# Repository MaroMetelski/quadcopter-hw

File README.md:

# Quadcopter flight controller

Brushed DC motor quadcopter flight controller hardware.

Schematics, PCB images and productions files for each release can be found
in https://github.com/MaroMetelski/quadcopter-hw/releases/.

# Revisions

## V1.0

Initial version of the brushed motor flight controller. Main features:

- 30.5x30.5 mm form factor
- Powered with 1S 3.7V battery
- On-board 1S Li-Po charger
- STM32F303RE controller
- Support for 6-channel PWM or 1-channel SBus radio receiver
- BQ274441 fuel gauge
- LSM6DSO 6-axis IMU (accelerometer & gyroscope)

Links:
- [Schematic](https://github.com/MaroMetelski/quadcopter-hw/releases/download/v1.0/quadcopter_v1.0_schematic.pdf)

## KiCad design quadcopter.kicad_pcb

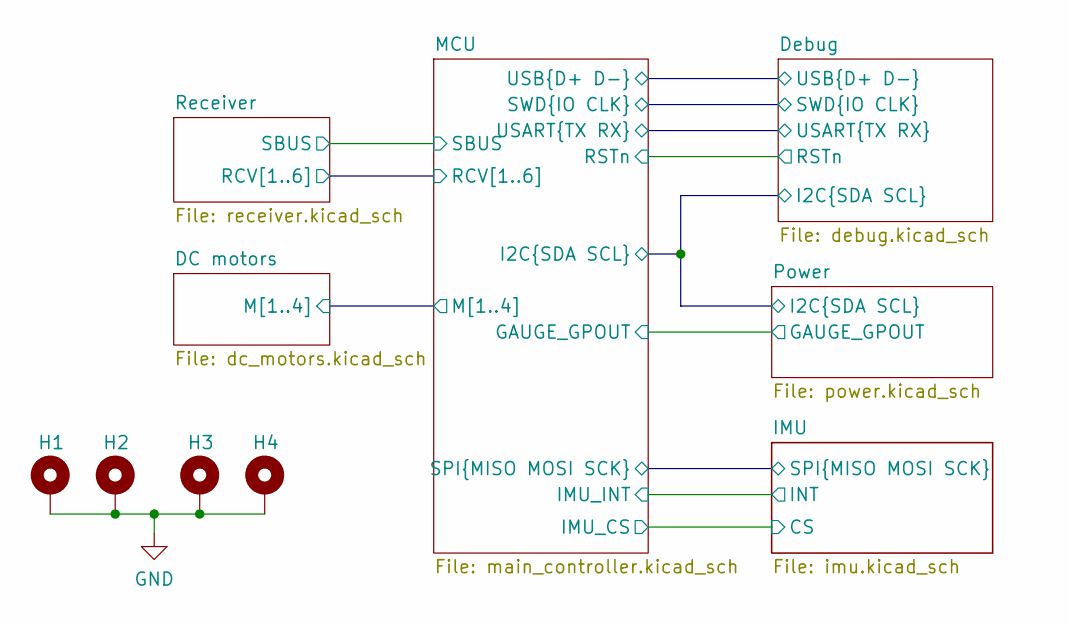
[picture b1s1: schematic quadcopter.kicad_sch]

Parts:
H1, H2, H3, H4: MountingHole_Pad; MountingHole_2.2mm_M2_Pad

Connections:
GND: H1.1, H2.1, H3.1, H4.1; also elsewhere on the board

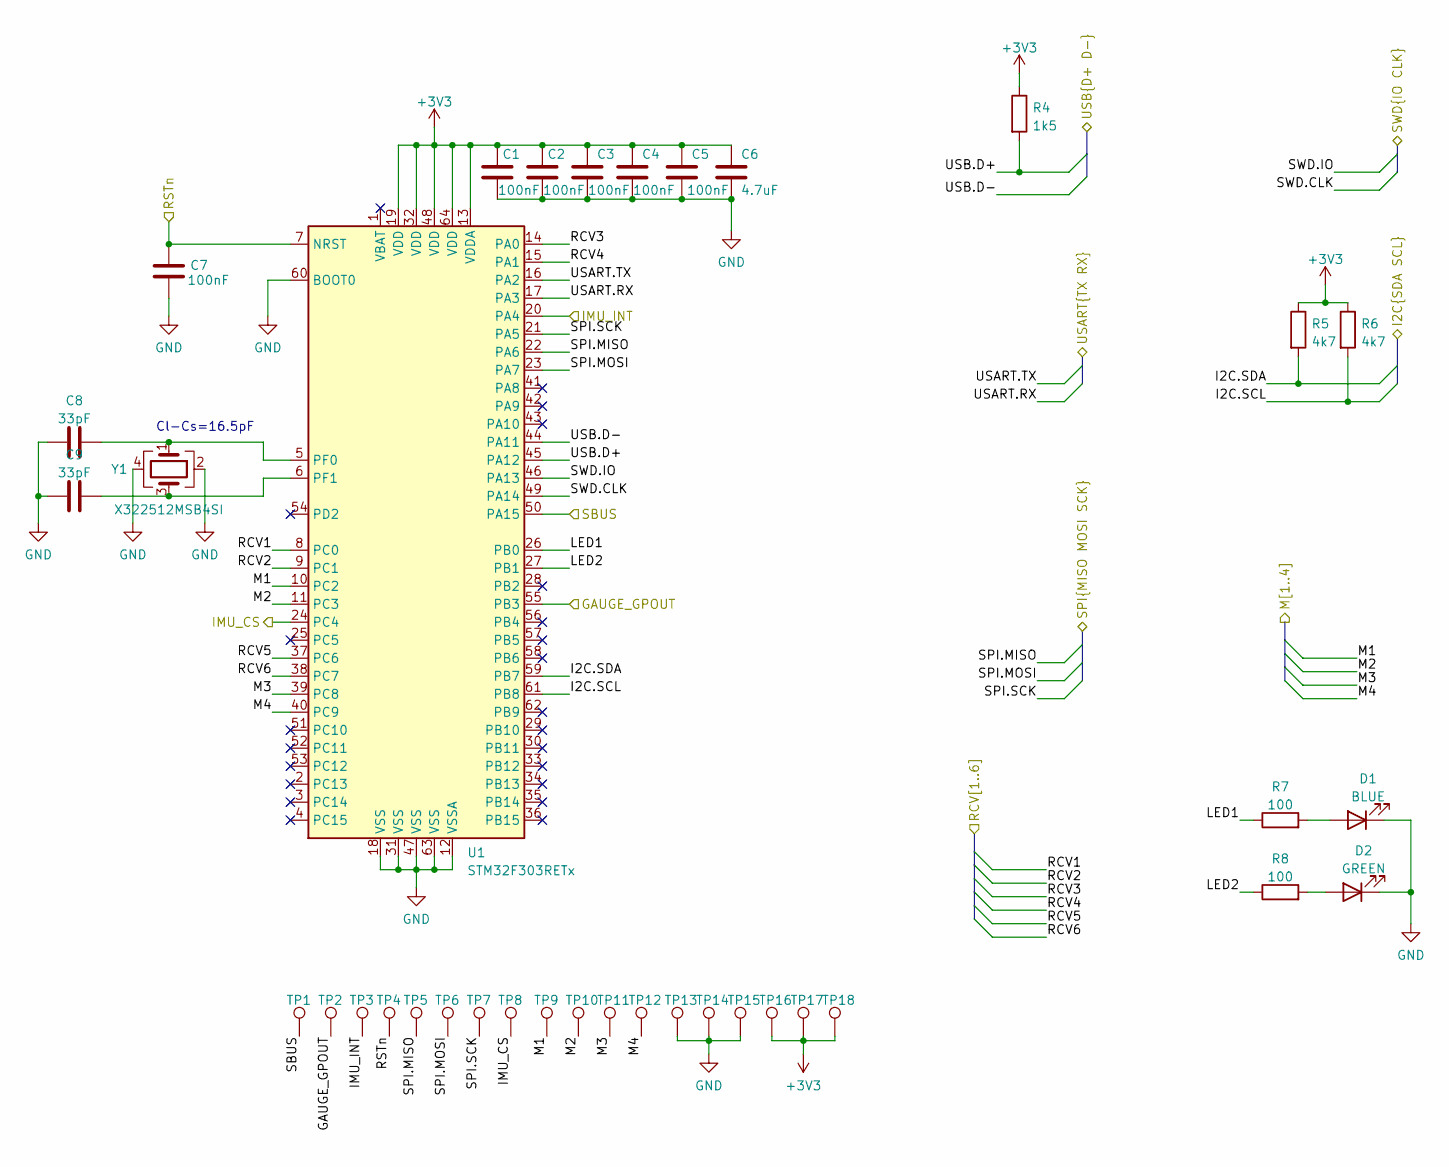
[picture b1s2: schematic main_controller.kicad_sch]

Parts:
C1, C2, C3, C4, C5, C7: 100nF; C_0402_1005Metric; JLC 0402
C6: 4.7uF; C_0402_1005Metric; JLC 0402
C8, C9: 33pF; C_0402_1005Metric; JLC 0402
D1: BLUE; LED_0603_1608Metric; JLC 0603
D2: GREEN; LED_0603_1608Metric; JLC 0603
R4: 1k5; R_0402_1005Metric; JLC 0402
R5, R6: 4k7; R_0402_1005Metric; JLC 0402
R7, R8: 100; R_0402_1005Metric; JLC 0402
TP1, TP2, TP3, TP4, TP5, TP6, TP7, TP8, TP9, TP10, TP11, TP12, TP13, TP14, TP15, TP16, TP17, TP18: TestPoint; TestPoint_Pad_D1.0mm
U1: STM32F303RETx; LQFP-64_10x10mm_P0.5mm; JLC LQFP-64(10x10)
Y1: X322512MSB4SI; Crystal_SMD_3225-4Pin_3.2x2.5mm; JLC SMD3225-4P

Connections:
+3V3: C1.1, C2.1, C3.1, C4.1, C5.1, C6.1, R4.1, R5.1, R6.1, TP16.1, TP17.1, TP18.1, U1.13 (VDDA), U1.19 (VDD), U1.32 (VDD), U1.48 (VDD), U1.64 (VDD); also elsewhere on the board
/DC motors/M1: TP9.1, U1.10 (PC2); also elsewhere on the board
/DC motors/M2: TP10.1, U1.11 (PC3); also elsewhere on the board
/DC motors/M3: TP11.1, U1.39 (PC8); also elsewhere on the board
/DC motors/M4: TP12.1, U1.40 (PC9); also elsewhere on the board
/Debug/I2C.SCL: R6.2, U1.61 (PB8); also elsewhere on the board
/Debug/I2C.SDA: R5.2, U1.59 (PB7); also elsewhere on the board
/Debug/SWD.CLK: U1.49 (PA14); also elsewhere on the board
/Debug/SWD.IO: U1.46 (PA13); also elsewhere on the board
/Debug/USART.RX: U1.17 (PA3); also elsewhere on the board
/Debug/USART.TX: U1.16 (PA2); also elsewhere on the board
/Debug/USB.D+: R4.2, U1.45 (PA12); also elsewhere on the board
/Debug/USB.D-: U1.44 (PA11); also elsewhere on the board
/IMU/SPI.MISO: TP5.1, U1.22 (PA6); also elsewhere on the board
/IMU/SPI.MOSI: TP6.1, U1.23 (PA7); also elsewhere on the board
/IMU/SPI.SCK: TP7.1, U1.21 (PA5); also elsewhere on the board
/MCU/GAUGE_GPOUT: TP2.1, U1.55 (PB3); also elsewhere on the board
/MCU/IMU_CS: TP8.1, U1.24 (PC4); also elsewhere on the board
/MCU/IMU_INT: TP3.1, U1.20 (PA4); also elsewhere on the board
/MCU/LED1: R7.1, U1.26 (PB0)
/MCU/LED2: R8.1, U1.27 (PB1)
/MCU/RCV1: U1.8 (PC0); also elsewhere on the board
/MCU/RCV2: U1.9 (PC1); also elsewhere on the board
/MCU/RCV3: U1.14 (PA0); also elsewhere on the board
/MCU/RCV4: U1.15 (PA1); also elsewhere on the board
/MCU/RCV5: U1.37 (PC6); also elsewhere on the board
/MCU/RCV6: U1.38 (PC7); also elsewhere on the board
/MCU/RSTn: C7.1, TP4.1, U1.7 (NRST); also elsewhere on the board
/MCU/SBUS: TP1.1, U1.50 (PA15); also elsewhere on the board
GND: C1.2, C2.2, C3.2, C4.2, C5.2, C6.2, C7.2, C8.1, C9.1, D1.1 (K), D2.1 (K), TP13.1, TP14.1, TP15.1, U1.12 (VSSA), U1.18 (VSS), U1.31 (VSS), U1.47 (VSS), U1.60 (BOOT0), U1.63 (VSS), Y1.2, Y1.4; also elsewhere on the board
unnamed: C8.2, U1.5 (PF0), Y1.1
unnamed: C9.2, U1.6 (PF1), Y1.3
unnamed: D1.2 (A), R7.2
unnamed: D2.2 (A), R8.2

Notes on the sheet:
Cl-Cs=16.5pF

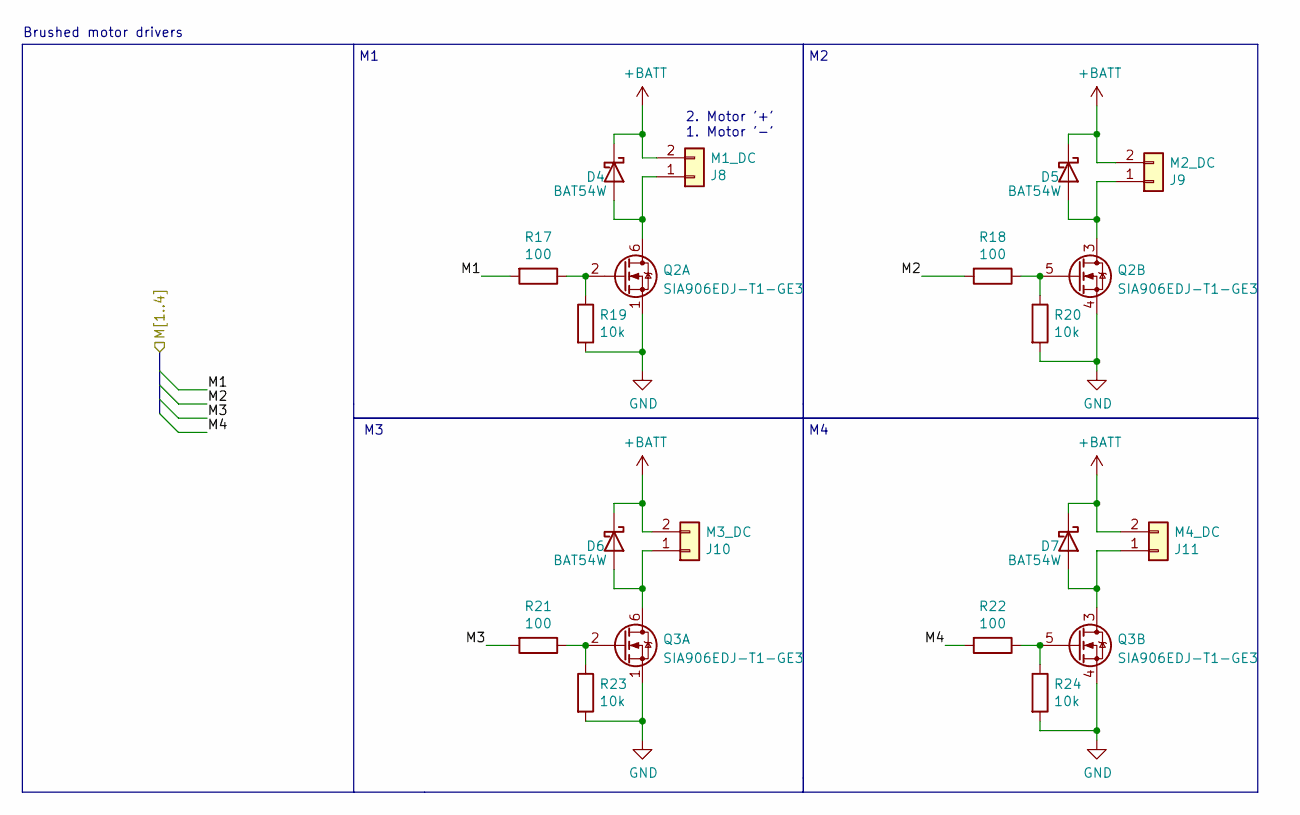
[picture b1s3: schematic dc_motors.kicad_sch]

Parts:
D4, D5, D6, D7: BAT54W; D_SOD-123; LCSC C915628
J8: M1_DC; PinHeader_1x02_P2.54mm_Vertical
J9: M2_DC; PinHeader_1x02_P2.54mm_Vertical
J10: M3_DC; PinHeader_1x02_P2.54mm_Vertical
J11: M4_DC; PinHeader_1x02_P2.54mm_Vertical
Q2, Q3: SIA906EDJ-T1-GE3; Vishay_PowerPAK_SC70-6L_Dual; JLC WSON-6-EP(2x2)
R17, R18, R21, R22: 100; R_0402_1005Metric; JLC 0402
R19, R20, R23, R24: 10k; R_0402_1005Metric; JLC 0402

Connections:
+BATT: D4.1 (K), D5.1 (K), D6.1 (K), D7.1 (K), J8.2, J9.2, J10.2, J11.2; also elsewhere on the board
/DC motors/M1: R17.2; also elsewhere on the board
/DC motors/M2: R18.2; also elsewhere on the board
/DC motors/M3: R21.2; also elsewhere on the board
/DC motors/M4: R22.2; also elsewhere on the board
GND: Q2.1 (S), Q2.4 (S), Q3.1 (S), Q3.4 (S), R19.2, R20.2, R23.2, R24.2; also elsewhere on the board
unnamed: D4.2 (A), J8.1, Q2.6 (D)
unnamed: D5.2 (A), J9.1, Q2.3 (D)
unnamed: D6.2 (A), J10.1, Q3.6 (D)
unnamed: D7.2 (A), J11.1, Q3.3 (D)
unnamed: Q2.2 (G), R17.1, R19.1
unnamed: Q2.5 (G), R18.1, R20.1
unnamed: Q3.2 (G), R21.1, R23.1
unnamed: Q3.5 (G), R22.1, R24.1

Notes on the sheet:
2. Motor '+' 1. Motor '-'
Brushed motor drivers

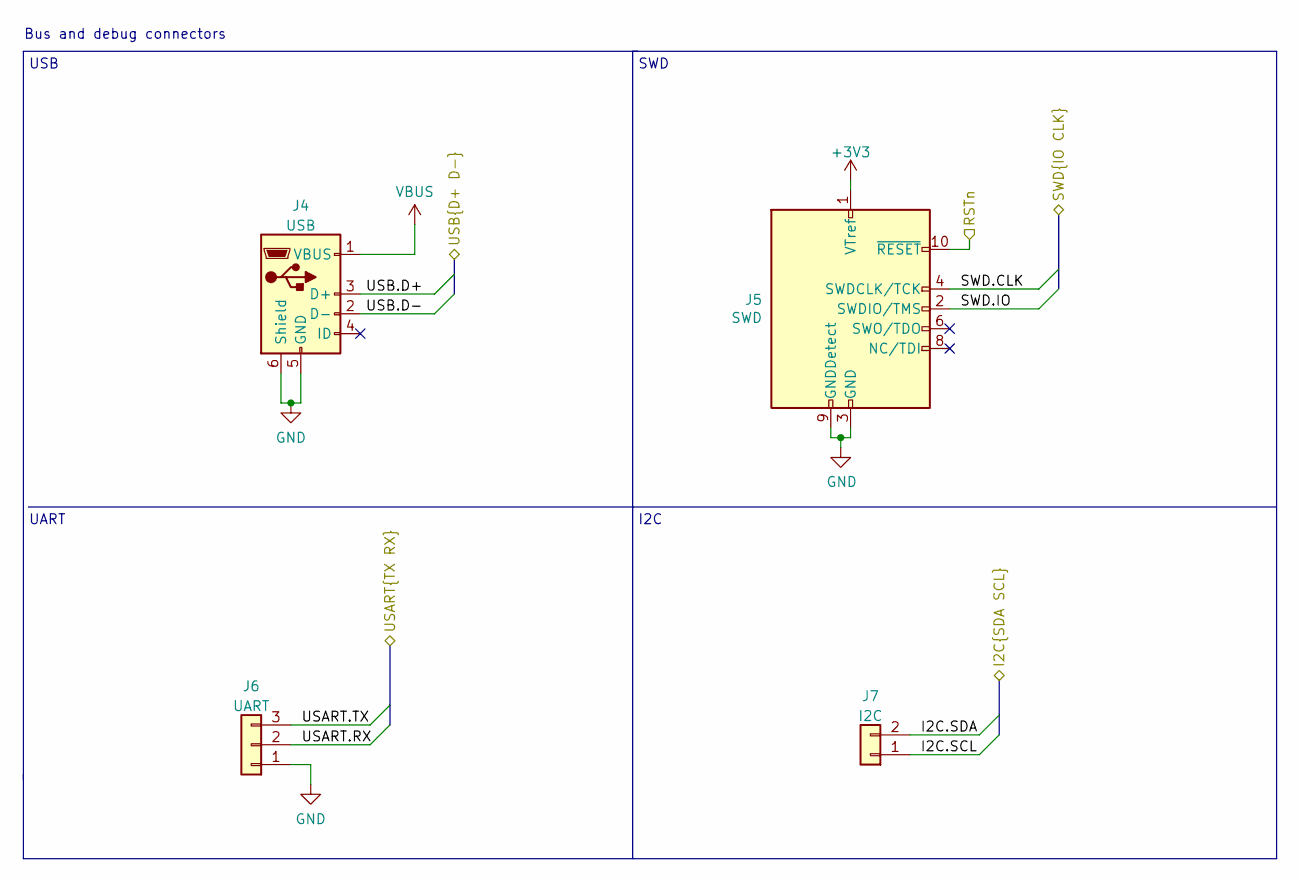
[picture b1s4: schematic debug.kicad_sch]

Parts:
J4: USB; USB_Micro-B_Molex-105017-0001; JLC SMD
J5: SWD; PinHeader_2x05_P1.27mm_Vertical_SMD
J6: UART; PinHeader_1x03_P2.54mm_Vertical
J7: I2C; PinHeader_1x02_P2.54mm_Vertical

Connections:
+3V3: J5.1 (VTref); also elsewhere on the board
/Debug/I2C.SCL: J7.1; also elsewhere on the board
/Debug/I2C.SDA: J7.2; also elsewhere on the board
/Debug/SWD.CLK: J5.4 (SWDCLK/TCK); also elsewhere on the board
/Debug/SWD.IO: J5.2 (SWDIO/TMS); also elsewhere on the board
/Debug/USART.RX: J6.2; also elsewhere on the board
/Debug/USART.TX: J6.3; also elsewhere on the board
/Debug/USB.D+: J4.3 (D+); also elsewhere on the board
/Debug/USB.D-: J4.2 (D-); also elsewhere on the board
/MCU/RSTn: J5.10 (~RESET); also elsewhere on the board
GND: J4.5 (GND), J4.6 (Shield), J5.3 (GND), J5.5 (GND), J5.9 (GNDDetect), J6.1; also elsewhere on the board
VBUS: J4.1 (VBUS); also elsewhere on the board

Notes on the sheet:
Bus and debug connectors
UART
I2C
USB
SWD

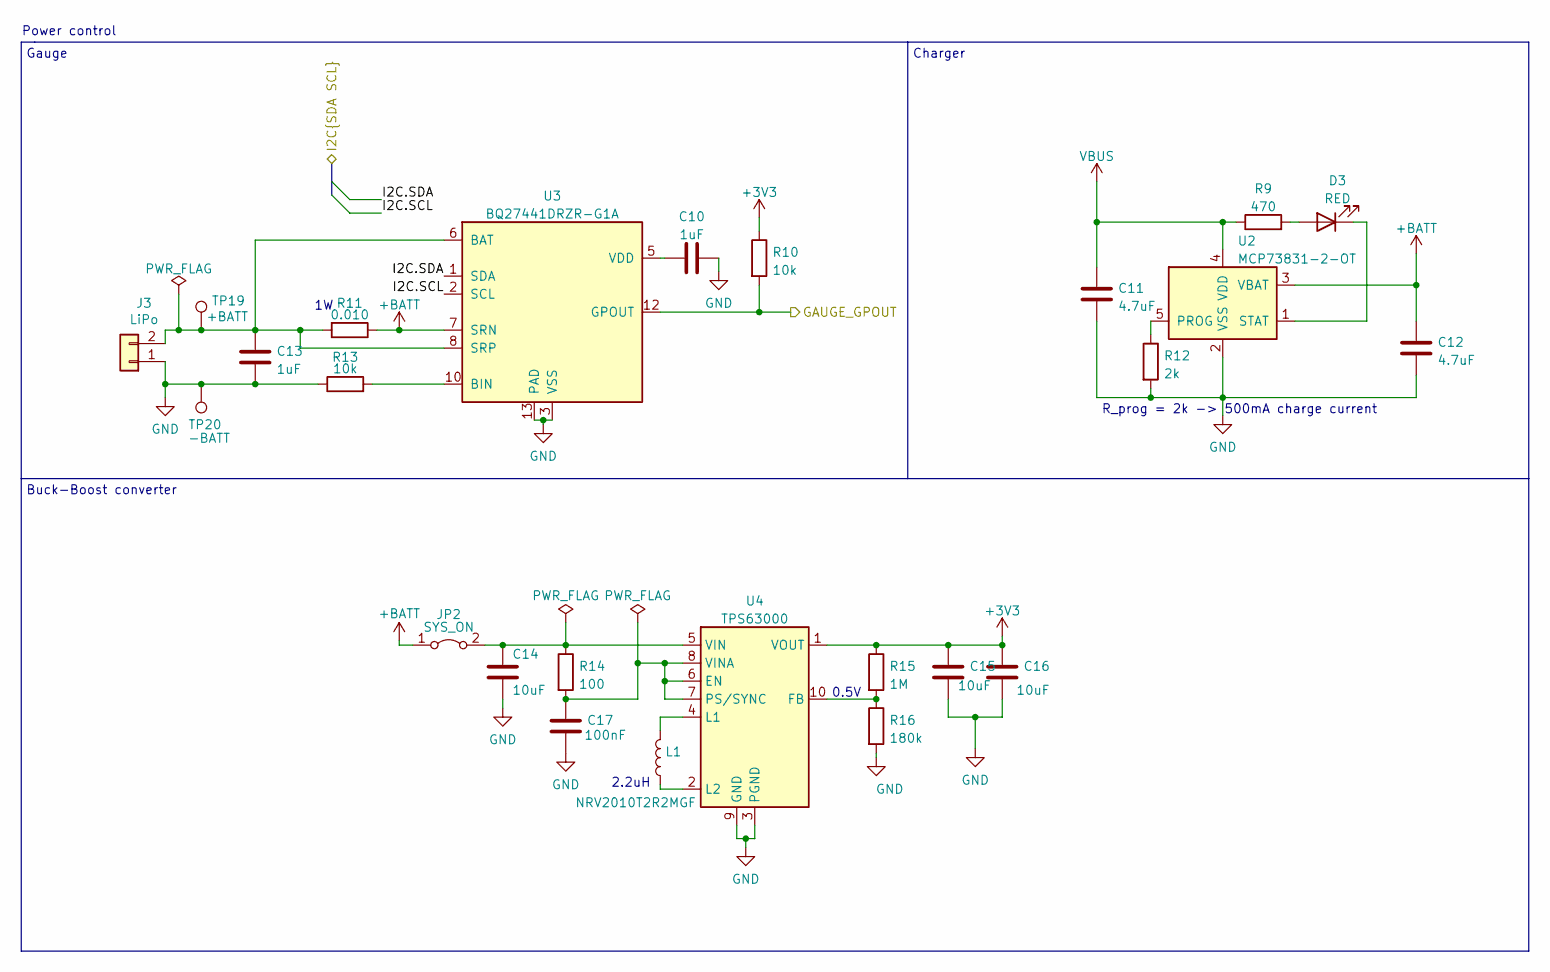
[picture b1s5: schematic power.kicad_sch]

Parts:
C10, C13: 1uF; C_0402_1005Metric; JLC 0402
C11, C12: 4.7uF; C_0402_1005Metric; JLC 0402
C14, C15, C16: 10uF; C_0402_1005Metric; JLC 0402
C17: 100nF; C_0402_1005Metric; JLC 0402
D3: RED; LED_0603_1608Metric; JLC 0603
J3: LiPo; PinHeader_1x02_P2.54mm_Vertical
JP2: SYS_ON; PinHeader_1x02_P2.54mm_Vertical
L1: NRV2010T2R2MGF; L_Taiyo-Yuden_NR-20xx; JLC SMD
R9: 470; R_0402_1005Metric; JLC 0402
R10, R13: 10k; R_0402_1005Metric; JLC 0402
R11: 0.010; R_2010_5025Metric; JLC 2010
R12: 2k; R_0402_1005Metric; JLC 0402
R14: 100; R_0402_1005Metric; JLC 0402
R15: 1M; R_0402_1005Metric; JLC 0402
R16: 180k; R_0402_1005Metric; JLC 0402
TP19: +BATT; TestPoint_Pad_2.0x2.0mm
TP20: -BATT; TestPoint_Pad_2.0x2.0mm
U2: MCP73831-2-OT; SOT-23-5; JLC SOT-23-5
U3: BQ27441DRZR-G1A; Texas_S-PDSO-N12; JLC SON-12-EP(2.5x4)
U4: TPS63000; Texas_DRC0010J_ThermalVias; JLC SON-10-EP(3.1x3.1)

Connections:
+3V3: C15.1, C16.1, R10.1, R15.1, U4.1 (VOUT); also elsewhere on the board
+BATT: C12.1, JP2.1 (A), R11.1, U2.3 (VBAT), U3.7 (SRN); also elsewhere on the board
/Debug/I2C.SCL: U3.2 (SCL); also elsewhere on the board
/Debug/I2C.SDA: U3.1 (SDA); also elsewhere on the board
/MCU/GAUGE_GPOUT: R10.2, U3.12 (GPOUT); also elsewhere on the board
GND: C10.2, C11.2, C12.2, C13.2, C14.2, C15.2, C16.2, C17.2, J3.1, R12.2, R13.1, R16.2, TP20.1, U2.2 (VSS), U3.3 (VSS), U3.13 (PAD), U4.3 (PGND), U4.9 (GND), U4.11 (PGND); also elsewhere on the board
unnamed: C10.1, U3.5 (VDD)
unnamed: C13.1, J3.2, R11.2, TP19.1, U3.6 (BAT), U3.8 (SRP)
unnamed: C14.1, JP2.2 (B), R14.1, U4.5 (VIN)
unnamed: C17.1, R14.2, U4.6 (EN), U4.7 (PS/SYNC), U4.8 (VINA)
unnamed: D3.1 (K), U2.1 (STAT)
unnamed: D3.2 (A), R9.2
unnamed: L1.1, U4.2 (L2)
unnamed: L1.2, U4.4 (L1)
unnamed: R12.1, U2.5 (PROG)
unnamed: R13.2, U3.10 (BIN)
unnamed: R15.2, R16.1, U4.10 (FB)
VBUS: C11.1, R9.1, U2.4 (VDD); also elsewhere on the board

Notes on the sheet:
2.2uH
Charger
R_prog = 2k -> 500mA charge current
Gauge
Power control
Buck-Boost converter
0.5V

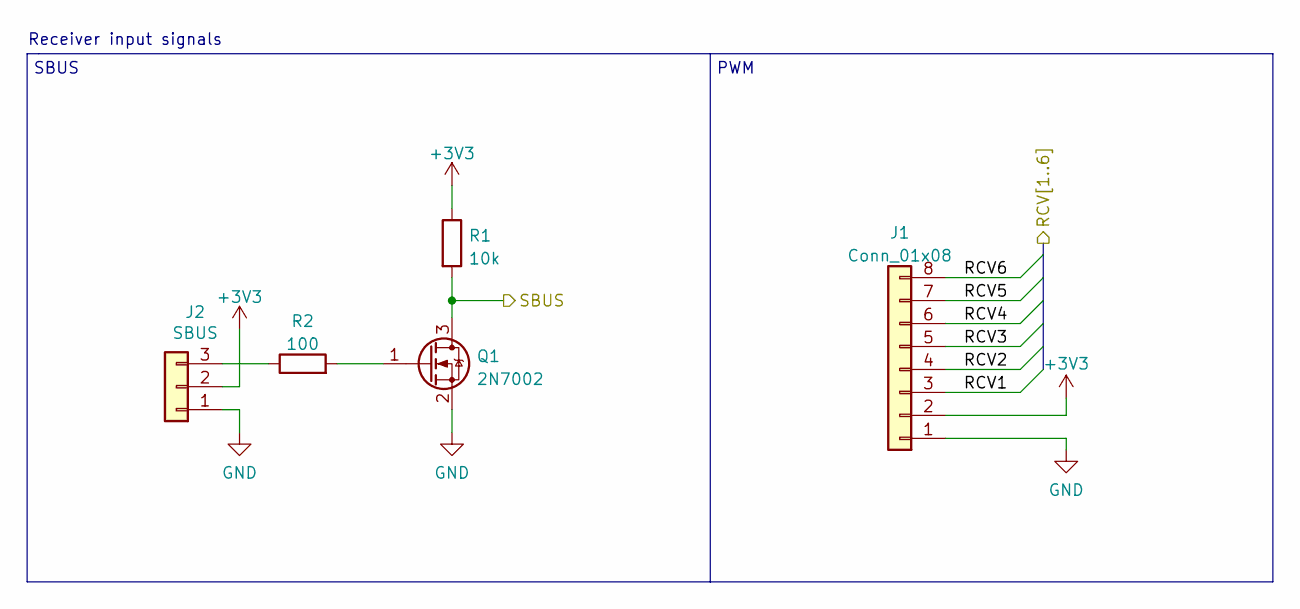
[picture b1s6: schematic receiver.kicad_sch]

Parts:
J1: Conn_01x08; PinHeader_1x08_P2.54mm_Vertical
J2: SBUS; PinHeader_1x03_P2.54mm_Vertical
Q1: 2N7002; SOT-23; JLC SOT-23
R1: 10k; R_0402_1005Metric; JLC 0402
R2: 100; R_0402_1005Metric; JLC 0402

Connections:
+3V3: J1.2, J2.2, R1.1; also elsewhere on the board
/MCU/RCV1: J1.3; also elsewhere on the board
/MCU/RCV2: J1.4; also elsewhere on the board
/MCU/RCV3: J1.5; also elsewhere on the board
/MCU/RCV4: J1.6; also elsewhere on the board
/MCU/RCV5: J1.7; also elsewhere on the board
/MCU/RCV6: J1.8; also elsewhere on the board
/MCU/SBUS: Q1.3 (D), R1.2; also elsewhere on the board
GND: J1.1, J2.1, Q1.2 (S); also elsewhere on the board
unnamed: J2.3, R2.1
unnamed: Q1.1 (G), R2.2

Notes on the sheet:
Receiver input signals
PWM
SBUS

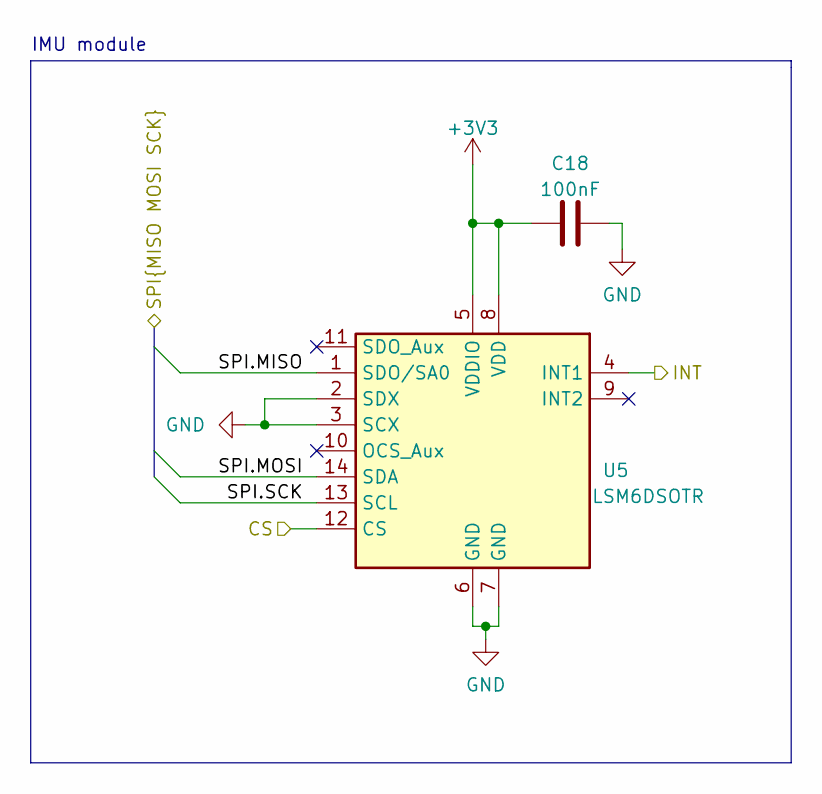
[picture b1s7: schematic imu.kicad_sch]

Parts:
C18: 100nF; C_0402_1005Metric; JLC 0402
U5: LSM6DSOTR; LGA-14_3x2.5mm_P0.5mm_LayoutBorder3x4y; JLC LGA-14(2.5x3)

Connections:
+3V3: C18.2, U5.5 (VDDIO), U5.8 (VDD); also elsewhere on the board
/IMU/SPI.MISO: U5.1 (SDO/SA0); also elsewhere on the board
/IMU/SPI.MOSI: U5.14 (SDA); also elsewhere on the board
/IMU/SPI.SCK: U5.13 (SCL); also elsewhere on the board
/MCU/IMU_CS: U5.12 (CS); also elsewhere on the board
/MCU/IMU_INT: U5.4 (INT1); also elsewhere on the board
GND: C18.1, U5.2 (SDX), U5.3 (SCX), U5.6 (GND), U5.7 (GND); also elsewhere on the board

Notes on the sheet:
IMU module

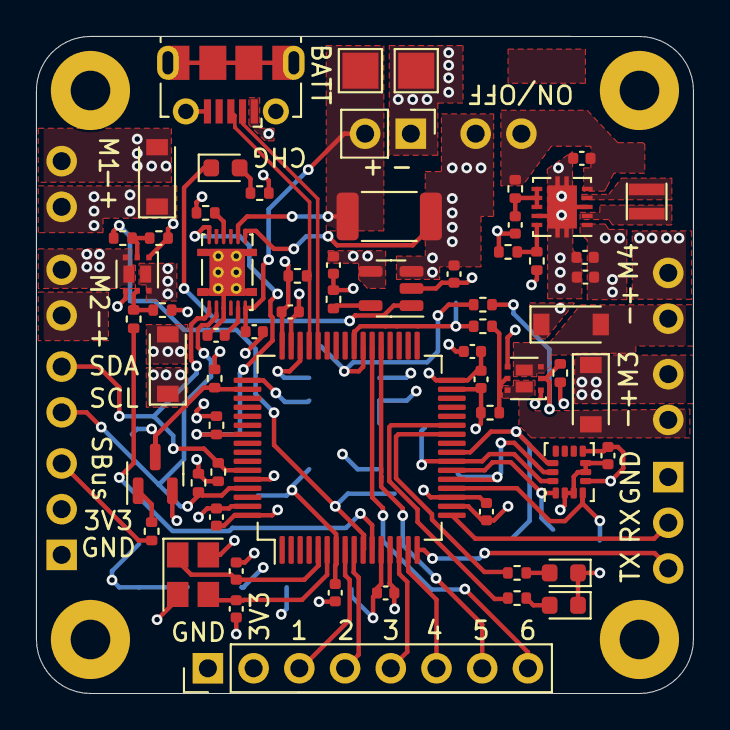
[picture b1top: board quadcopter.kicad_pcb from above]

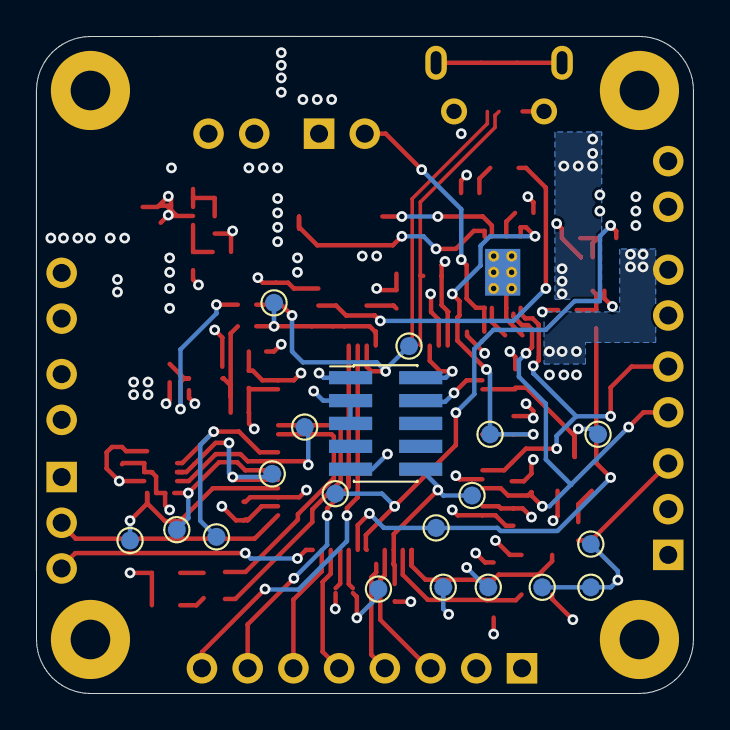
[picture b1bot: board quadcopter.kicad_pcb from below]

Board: 4 copper layers, 36.5 x 36.5 mm, 94 parts (19 on the bottom side), 57 nets.

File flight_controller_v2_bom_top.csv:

"Comment","Designator","Footprint","LCSC Part #"
"Conn_01x08","J1","",""
"SBUS","J2","",""
"2N7002","Q1","SOT-23","C8545"
"10k","R1 R3 R10 R13 R20 R23 R24","0402"," C25744"
"100","R2 R7 R8 R14 R17 R18 R21 R22","0402"," C25076"
"100nF","C1 C2 C3 C4 C5 C7 C17 C18","0402","C1525"
"4.7uF","C6 C11 C12","0402","C23733"
"33pF","C8 C9","0402","C1562"
"BLUE","D1","0603","C72041"
"GREEN","D2","0603","C72043"
"FWU","JP1","",""
"1k5","R4","0402"," C25867"
"4k7","R5 R6","0402"," C25900"
"STM32F303RETx","U1","LQFP-64(10x10)","C183214"
"X322512MSB4SI","Y1","SMD3225-4P","C9002"
"1uF","C10 C13","0402","C52923"
"10uF","C14 C15 C16","0402","C15525"
"RED","D3","0603","C2286"
"LiPo","J3","",""
"SYS_ON","JP2","",""
"NRV2010T2R2MGF","L1","SMD","C222837"
"470","R9","0402","C25117"
"0.010","R11","2010","C175965"
"2k","R12","0402","C4109"
"1M","R15","0402","C26083"
"180k","R16","0402"," C25760 "
"MCP73831-2-OT","U2","SOT-23-5","C424093"
"BQ27441DRZR-G1A","U3","SON-12-EP(2.5x4)","C473397"
"TPS63000","U4","SON-10-EP(3.1x3.1)","C24966"
"USB","J4","SMD","C136000"
"UART","J6","",""
"I2C","J7","",""
"BAT54W","D4 D5 D6 D7","SOD-123","C915628"
"M1_DC","J8","",""
"M2_DC","J9","",""
"M3_DC","J10","",""
"M4_DC","J11","",""
"SIA906EDJ-T1-GE3","Q2 Q3","WSON-6-EP(2x2)","C142544"
"10k","R19","0402",""
"LSM6DSOTR","U5","LGA-14(2.5x3)","C2655100"

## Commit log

2023-01-12 Remove and ignore *-backups
2023-01-12 Add QSPI flash
2023-06-05 Initial schematic version
    This is now a clean and ready version of the schematic:
    That means:
    - Schematic has been reviewed,
    - It's fully annotated,
    - All elements have been checked for availability with JLCPCB,
    - Footprints were assigned,
2023-06-05 Update footprints and add JLCPCB fields
    Update some footprints which will suit better building the pcb
    with JLCBPCB. Add fields to components sourced from JLCPCB
    to be able to generate BOM.
2023-06-05 Genarate JLCPCB BOM
    Add BOM compatible with JLCPCB. This allows to already check and / or
    source all the components.
    The BOM was generated using this script:
    https://github.com/djmdjm/KiJLC
    A modification was needed to change board.GetModules() to
    board.Footprints() in the script.
2023-06-05 Rename project to 'quadcopter'
    'flight_controller_v2' was the code name for the project based
    on the fact that there was a development version 'v1' of the PCB
    designed in Eagle which was not really mature. Except for the idea
    this is a completely new project - KiCAD, different components etc.
    Use generic name 'quadcopter' for now until the projects grows
    to an actual product.
2023-06-05 fix: Fix D4-D7 schottky mismatch between symbol and footprint
    Symbol was placed for diode in SOT-323 package with 3 pins, but
    2 pin footprint was assigned. Use generic symbol with two pins.
2023-06-22 Add finished PCB design for initial release
    This is quite a messy version of the initial PCB, hopefully without
    errors. Should conform to JLCPCB manufacturing process.
    This is a 4 layer PCB with components on the TOP, test pads and
    placement for debug connector on the bottom.
    The inside layers consist of a ground plane and a layer for power
    signals, especially 3v3 and BATT.
2023-06-22 Delete BOM files
    BOM files will be a part of the release package.
2023-06-22 [WIP] assembly drawing
2024-11-22 Add README file
    Add README with basic information about the project.
2025-03-14 license: Release project under CERN OHL V2 permissive license
    Release project under CERN Open Hardware Licence Version 2 - permissive.
